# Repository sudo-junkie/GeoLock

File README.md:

# GeoLock

KiCad 7 design files (schematic, PCB, BOM, gerbers) for an STM32F103-based car tracker with the following features:

-	USB-C - firmware upload & debugging
-	Relay - for engine cutout
-	NEO-6M GPS - location tracking
-	SIM800C GSM - for text-based killswitch and location reporting
-	SD Card - location logging and saving persistent settings/data

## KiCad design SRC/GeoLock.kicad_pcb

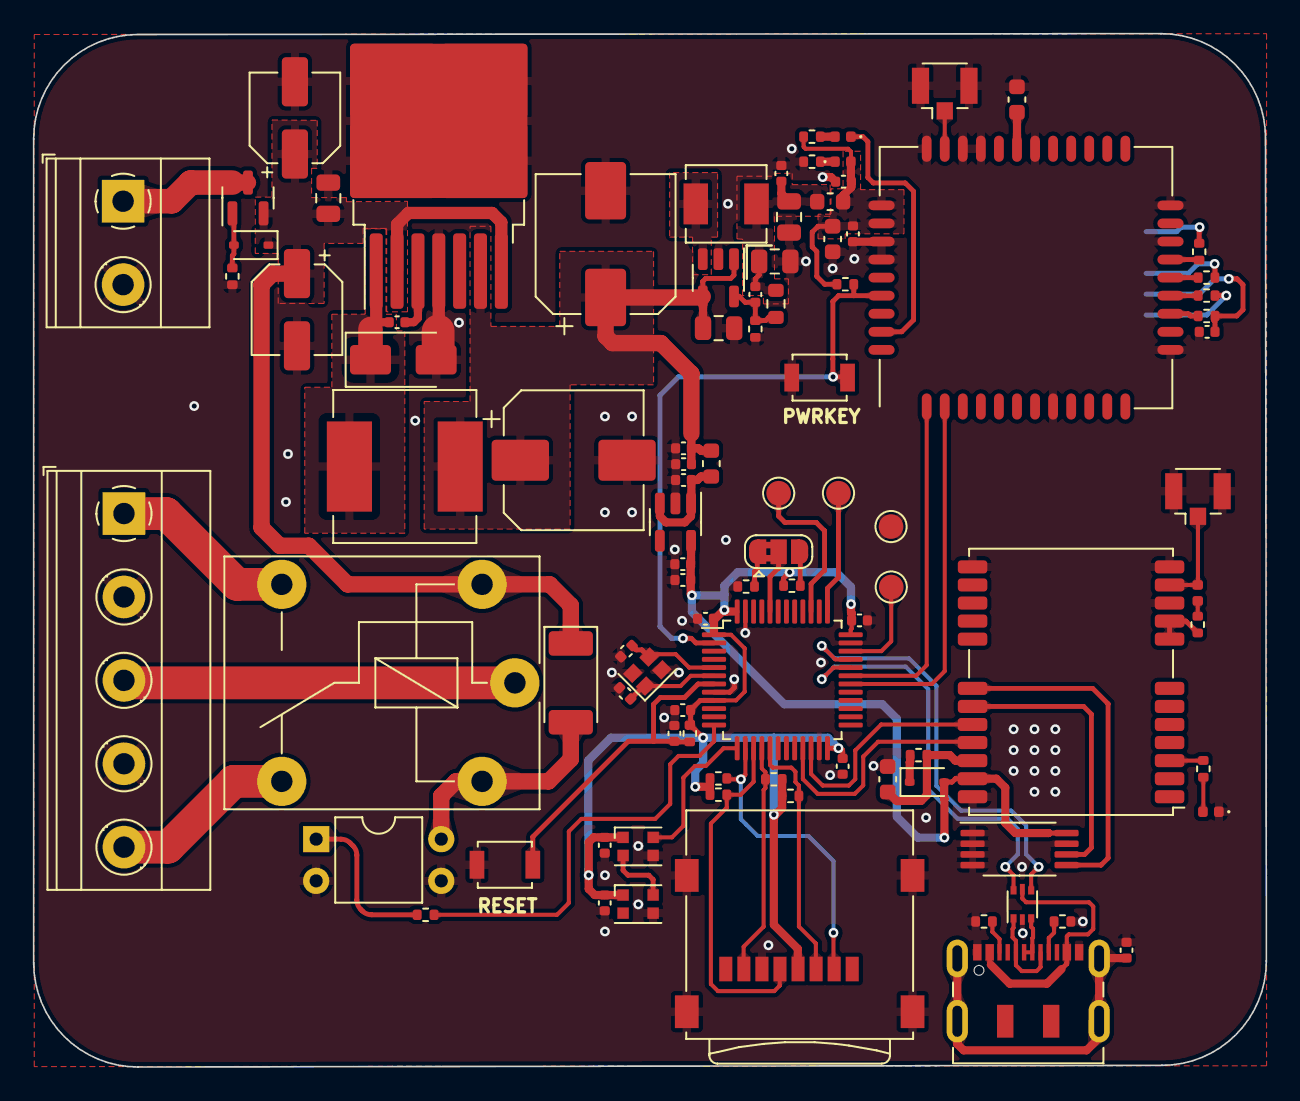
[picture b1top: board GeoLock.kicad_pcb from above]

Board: 2 copper layers, 75.1 x 62.9 mm, 95 parts (1 on the bottom side), 69 nets.

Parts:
C101, C207, C409, C410, C508, C509, C510: 1u 10% 10V X5R; C_0402_1005Metric
C203: 10u 20% 10V X5R; C_0402_1005Metric
C204, C205, C206, C210, C211, C404, C507, C511: 100n 10V 5%; C_0402_1005Metric
C208, C209: 22p 1% NP0 50V; C_0402_1005Metric
C401, C403, C601: 100u 20% 6.3V; C_0603_1608Metric
C402, C408: 8p ±1% 50V C0G; C_0402_1005Metric
C405, C406, C407: 22u 20% X5R 16V; C_0805_2012Metric
C501: 10n 5% 16V X7R; C_0402_1005Metric
C502, C503: 22u 20% 50V; CP_Elec_5x5.8
C504: 470n 5% 50V X7R; C_0805_2012Metric
C505, C506: 180u 20% 50V; CP_Elec_8x10
D101: 11V; D_SOD-323
D201, D202: WS2812B; LED_WS2812B-2020_PLCC4_2.0x2.0mm
D301: SM4001; D_MELF
D401: GSM_PWR; LED_0402_1005Metric
D402: GSM_NET; LED_0402_1005Metric
D501: SS54; D_SMA
D601: SD103AWS; D_SOD-323
D602: LED_GPS; LED_0402_1005Metric
FB401, FB501: 220R @ 100MHz 3A; L_0603_1608Metric
J101: Conn_VIN; TerminalBlock_Phoenix_MKDS-1,5-2-5.08_1x02_P5.08mm_Horizont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
J102: Conn_CUTOUT; TerminalBlock_Phoenix_MKDS-1,5-5-5.08_1x05_P5.08mm_Horizont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
J103: USB_C_Receptacle_USB2.0; USB_C_Receptacle_JAE_DX07S016JA1R1500
J201: Micro_SD_Card; microSD_HC_Wuerth_693072010801
J401: SIM_Card; microSIM_JAE_SF53S006VCBR2000
J402: Conn_GSM; U.FL_Hirose_U.FL-R-SMT-1_Vertical
J601: Conn_GPS; U.FL_Hirose_U.FL-R-SMT-1_Vertical
JP201: JP_BOOT; SolderJumper-3_P1.3mm_Bridged2Bar12_RoundedPad1.0x1.5mm
K301: FINDER-36.11; Relay_SPDT_Finder_36.11
L401: 2u2; L_Sunlord_MWSA0402S
L501: 22u; L_Sunlord_MWSA0804S
L601: 22u; L_0402_1005Metric
Q101: AO3401A; SOT-23
R101, R201, R202, R203, R204, R205, R206, R207, R407: 10K 0.1%; R_0402_1005Metric
R102, R103: 5K1 0.1%; R_0402_1005Metric
R301, R602: 1K 0.1%; R_0402_1005Metric
R401: 330K 0.1%; R_0603_1608Metric
R402: 56K 0.1%; R_0402_1005Metric
R403, R404, R405, R406: 51R 0.1%; R_0402_1005Metric
R408, R603: 4k7 0.1%; R_0402_1005Metric
R409: 4K7 0.1%; R_0402_1005Metric
R601: 22R 0.1%; R_0402_1005Metric
SW201: SW_RST; SW_SPST_B3U-1000P
SW401: GSM_PWR; SW_SPST_B3U-1000P
TP201: TP_SWCLK; TestPoint_Pad_D1.5mm
TP202: TP_GND; TestPoint_Pad_D1.5mm
TP203: TP_SWO; TestPoint_Pad_D1.5mm
TP204: TP_SWDIO; TestPoint_Pad_D1.5mm
U101: USBLC6-2P6; SOT-666
U201: STM32F103CBTx; LQFP-48_7x7mm_P0.5mm
U301: PC817; DIP-4_W7.62mm
U401: SY8089; SOT-23-5
U402: SIM800C; SIMCom_SIM800C
U501: LM2678-5.0; TO-263-7_TabPin8
U502: TLV75733PDBV; SOT-23-5
U601: NEO-6x; ublox_NEO
U602: 24LC32; TSSOP-8_4.4x3mm_P0.65mm
Y201: 16MHz; Crystal_SMD_2016-4Pin_2.0x1.6mm

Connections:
+3V3: C203.1, C204.1, C205.1, C206.1, C210.1, C211.1, C510.1, C511.1, D201.1 (VDD), D202.1 (VDD), D601.2 (A), J201.4 (VDD), R201.1, R202.1, R203.1, R204.1, R205.1, R206.1, U201.1 (VBAT), U201.9 (VDDA), U201.24 (VDD), U201.36 (VDD), U201.48 (VDD), U502.5 (OUT), U601.23 (VCC), U602.8 (VCC)
+4V: C403.2, C404.1, C410.1, D401.2 (A), FB401.1, R407.1, R408.2, U402.34 (VBAT), U402.35 (VBAT)
+5V: C405.1, C505.1, C506.1, C507.1, C508.1, FB501.1, L501.2, U401.1 (EN), U401.4 (VIN), U501.6 (FB)
+12V: C502.1, C503.1, C504.1, D101.1 (K), D301.1 (K), K301.A1, Q101.2 (S), U501.2 (VIN), U501.7 (EN)
/D+: J103.A6 (D+), J103.B6 (D+), U101.3 (I/O2)
/D-: J103.A7 (D-), J103.B7 (D-), U101.1 (I/O1)
/GeoLock_Power/SW_5V: C501.2, D501.1 (K), L501.1, U501.1 (SW)
/MCU_ST_STM32F103CBTx/BOOT0: JP201.2 (C), U201.44 (BOOT0)
/MCU_ST_STM32F103CBTx/HOSC1: C208.1, U201.5 (PD0), Y201.3
/MCU_ST_STM32F103CBTx/HOSC2: C209.1, U201.6 (PD1), Y201.1
/MCU_ST_STM32F103CBTx/LED_DIN: D201.4 (DIN), U201.13 (PA3)
/MCU_ST_STM32F103CBTx/NRST: C207.1, R201.2, SW201.2, U201.7 (NRST)
/MCU_ST_STM32F103CBTx/RELAY_EN: R301.1, U201.12 (PA2)
/MCU_ST_STM32F103CBTx/SD_CLK: J201.5 (CLK), R203.2, U201.15 (PA5)
/MCU_ST_STM32F103CBTx/SD_MISO: J201.7 (DAT0), R204.2, U201.16 (PA6)
/MCU_ST_STM32F103CBTx/SD_MOSI: J201.3 (CMD), R205.2, U201.17 (PA7)
/MCU_ST_STM32F103CBTx/SD_NCS: J201.2 (DAT3/CD), R202.2, U201.14 (PA4)
/MCU_ST_STM32F103CBTx/SWCLK: TP201.1, U201.37 (PA14)
/MCU_ST_STM32F103CBTx/SWDIO: TP204.1, U201.34 (PA13)
/MCU_ST_STM32F103CBTx/SWO: TP203.1, U201.39 (PB3)
/MCU_ST_STM32F103CBTx/USART1_RX: U201.31 (PA10), U402.1 (UART1_TXD)
/MCU_ST_STM32F103CBTx/USART1_TX: U201.30 (PA9), U402.2 (UART1_RXD)
/MCU_ST_STM32F103CBTx/USART3_RX: U201.22 (PB11), U601.20 (TXD1)
/MCU_ST_STM32F103CBTx/USART3_TX: U201.21 (PB10), U601.21 (RXD1)
/MODULE_RELAY/RELAY_NC: J102.5, K301.12
/MODULE_RELAY/RELAY_NO: J102.1, K301.14
/MODULE_RELAY/RELAY_POLE: J102.3, K301.11
/RF_GPS_NEO6M/GPS_RF: J601.1 (In), L601.2, U601.11 (RF_IN)
/RF_GPS_NEO6M/V_BCKP: C601.2, R602.2, U601.22 (V_BCKP)
/RF_GPS_NEO6M/V_RF: R601.1, U601.8 (VCC_RF), U601.9 (VCC_RF)
/RF_GSM_SIM800C/4V_OUT: C402.1, C406.1, C407.1, C409.1, FB401.2, L401.2, R401.1
/RF_GSM_SIM800C/4V_SW: L401.1, U401.3 (LX)
/RF_GSM_SIM800C/GSM_RF: J402.1 (In), U402.32 (GSM_ANT)
/RF_GSM_SIM800C/NETLIGHT: D402.1 (K), U402.41 (NETLIGHT)
/RF_GSM_SIM800C/PWRKEY: R407.2, SW401.1, U201.2 (PC13), U402.39 (~PWRKEY)
/RF_GSM_SIM800C/SIM_CLK: J401.3 (CLK), R405.2
/RF_GSM_SIM800C/SIM_DIO: C408.2, J401.7 (I/O), R404.2
/RF_GSM_SIM800C/SIM_RST: J401.2 (RST), R406.2
/RF_GSM_SIM800C/VSIM: J401.1 (VCC), R403.2
/USB_DN: U101.6 (I/O1), U201.32 (PA11)
/USB_DP: U101.4 (I/O2), U201.33 (PA12)
Earth: C101.1, J103.S1 (SHIELD)
GND: C101.2, C203.2, C204.2, C205.2, C206.2, C207.2, C208.2, C209.2, C210.2, C211.2, C401.1, C403.1, C404.2, C405.2, C406.2, C407.2, C408.1, C409.2, C410.2, C502.2, C503.2, C504.2, C505.2, C506.2, C507.2, C508.2, C509.2, C510.2, C511.2, C601.1, D201.3 (VSS), D202.3 (VSS), D501.2 (A), D602.1 (K), J101.2, J102.2, J102.4, J103.A1 (GND), J103.A12 (GND), J103.B1 (GND), J103.B12 (GND), J201.6 (VSS), J201.9 (SHIELD), J401.5 (GND), J401.SH, J402.2 (Ext), J601.2 (Ext), R101.2, R102.2, R103.2, R207.2, R402.2, R409.2, SW201.1, SW401.2, TP202.1, U101.2 (GND), U201.8 (VSSA), U201.23 (VSS), U201.35 (VSS), U201.47 (VSS), U301.2, U301.3, U401.2 (GND), U402.8 (GND), U402.13 (GND), U402.19 (GND), U402.21 (GND), U402.27 (GND), U402.30 (GND), U402.31 (GND), U402.33 (GND), U402.36 (GND), U402.37 (GND), U501.4 (GND), U501.8 (GND), U502.2 (GND), U601.10 (GND), U601.12 (GND), U601.13 (GND), U601.24 (GND), U602.1 (A0), U602.2 (A1), U602.3 (A2), U602.4 (GND), U602.7 (WP), Y201.2, Y201.4
unnamed: D101.2 (A), Q101.1 (G), R101.1
unnamed: D201.2 (DOUT), D202.4 (DIN)
unnamed: D301.2 (A), K301.A2, U301.4
unnamed: D401.1 (K), R409.1
unnamed: D402.2 (A), R408.1
unnamed: D601.1 (K), R602.1
unnamed: D602.2 (A), R603.1
unnamed: J101.1, Q101.3 (D)
unnamed: J103.A5 (CC1), R102.1
unnamed: J103.B5 (CC2), R103.1
unnamed: JP201.1 (A), R207.1
unnamed: JP201.3 (B), R206.2
unnamed: L601.1, R601.2
unnamed: R301.2, U301.1
unnamed: C402.2, R401.2, R402.1, U401.5 (FB)
unnamed: R405.1, U402.16 (SIM_CLK)
unnamed: R404.1, U402.15 (SIM_DATA)
unnamed: R406.1, U402.17 (SIM_RST)
unnamed: R403.1, U402.18 (SIM_VDD)
unnamed: C401.2, U402.28 (VRTC)
unnamed: C501.1, U501.3 (BOOST)
unnamed: C509.1, FB501.2, U502.1 (IN), U502.3 (EN)
unnamed: U601.19 (SCL2), U602.6 (SCL)
unnamed: U601.18 (SDA2), U602.5 (SDA)
unnamed: R603.2, U601.3 (TIMEPULSE)
VBUS: J103.A4 (VBUS), J103.A9 (VBUS), J103.B4 (VBUS), J103.B9 (VBUS), U101.5 (VBUS)

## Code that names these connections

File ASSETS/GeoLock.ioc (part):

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Mcu.Name=STM32F103C(8-B)Tx
Mcu.Package=LQFP48
Mcu.UserName=STM32F103CBTx
PA0-WKUP.Mode=SYS_WakeUp0
PA0-WKUP.Signal=SYS_WKUP
PA10.Mode=Asynchronous
PA10.Signal=USART1_RX
PA11.Mode=Device
PA11.Signal=USB_DM
PA12.Mode=Device
PA12.Signal=USB_DP
PA13.Mode=Trace_Asynchronous_SW
PA13.Signal=SYS_JTMS-SWDIO
PA14.Mode=Trace_Asynchronous_SW
PA14.Signal=SYS_JTCK-SWCLK
PA2.GPIOParameters=GPIO_Label
PA2.GPIO_Label=RELAY_EN
PA2.Signal=GPIO_Output
PA3.GPIOParameters=GPIO_Label
PA3.GPIO_Label=LED_DIN
PA3.Signal=GPIO_Output
PA4.GPIOParameters=GPIO_Label
PA4.GPIO_Label=SD_NCS
PA4.Signal=GPIO_Output
PA5.GPIOParameters=GPIO_Label
PA5.GPIO_Label=SD_CLK
PA5.Mode=Full_Duplex_Master
PA5.Signal=SPI1_SCK
PA6.GPIOParameters=GPIO_Label
PA6.GPIO_Label=SD_MISO
PA6.Mode=Full_Duplex_Master
PA6.Signal=SPI1_MISO
PA7.GPIOParameters=GPIO_Label
PA7.GPIO_Label=SD_MOSI
PA7.Mode=Full_Duplex_Master
PA7.Signal=SPI1_MOSI
PA9.Mode=Asynchronous
PA9.Signal=USART1_TX
PB10.Mode=Asynchronous
PB10.Signal=USART3_TX
PB11.Mode=Asynchronous
PB11.Signal=USART3_RX
PB3.Mode=Trace_Asynchronous_SW
PB3.Signal=SYS_JTDO-TRACESWO
PC13-TAMPER-RTC.GPIOParameters=GPIO_Label
PC13-TAMPER-RTC.GPIO_Label=GSM_PWRKEY
PC13-TAMPER-RTC.Signal=GPIO_Output
PD0-OSC_IN.Mode=HSE-External-Oscillator
PD0-OSC_IN.Signal=RCC_OSC_IN
PD1-OSC_OUT.Mode=HSE-External-Oscillator
PD1-OSC_OUT.Signal=RCC_OSC_OUT
RCC.SYSCLKFreq_VALUE=72000000
RCC.SYSCLKSource=RCC_SYSCLKSOURCE_PLLCLK
board=custom
